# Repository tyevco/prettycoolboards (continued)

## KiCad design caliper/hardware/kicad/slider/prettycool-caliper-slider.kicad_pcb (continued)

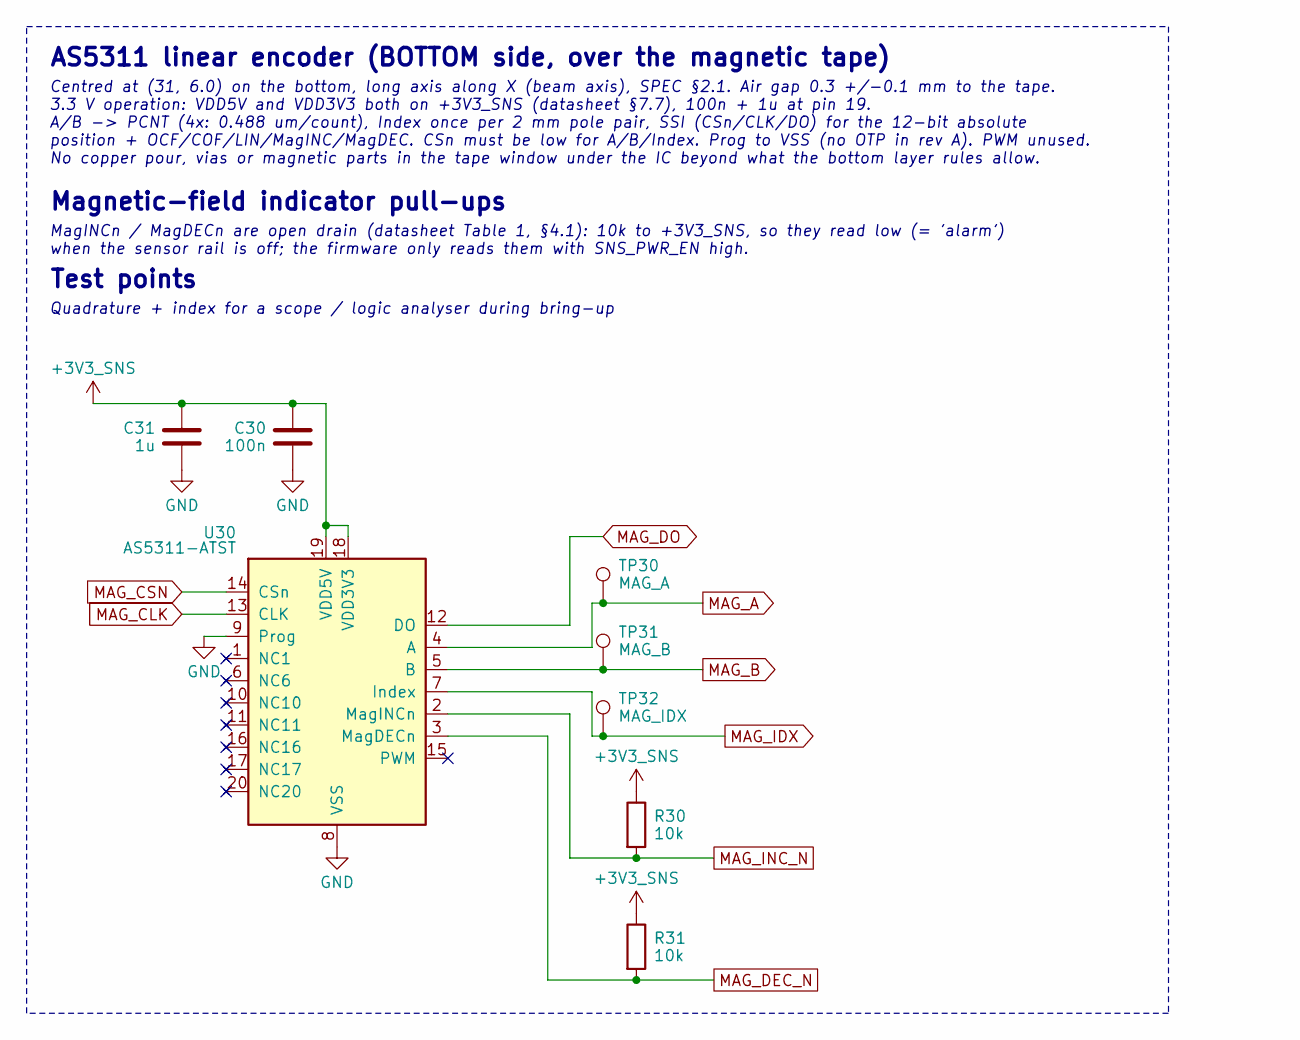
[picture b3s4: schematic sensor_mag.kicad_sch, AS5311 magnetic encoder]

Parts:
C30: 100n; C_0402_1005Metric; MPN CL05B104KO5NNNC; LCSC C1525
C31: 1u; C_0402_1005Metric; MPN CL05A105KA5NQNC; LCSC C52923
R30, R31: 10k; R_0402_1005Metric; MPN 0402WGF1002TCE; LCSC C25744
TP30: MAG_A; TestPoint_Pad_D1.0mm
TP31: MAG_B; TestPoint_Pad_D1.0mm
TP32: MAG_IDX; TestPoint_Pad_D1.0mm
U30: AS5311-ATST; TSSOP-20_4.4x6.5mm_P0.65mm; MPN AS5311-ATST; LCSC C22459687

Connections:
+3V3_SNS: C30.1, C31.1, R30.1, R31.1, U30.18 (VDD3V3), U30.19 (VDD5V); also elsewhere on the board
GND: C30.2, C31.2, U30.8 (VSS), U30.9 (Prog); also elsewhere on the board
MAG_A: TP30.1, U30.4 (A); also elsewhere on the board
MAG_B: TP31.1, U30.5 (B); also elsewhere on the board
MAG_CLK: U30.13 (CLK); also elsewhere on the board
MAG_CSN: U30.14 (CSn); also elsewhere on the board
MAG_DEC_N: R31.2, U30.3 (MagDECn); also elsewhere on the board
MAG_DO: U30.12 (DO); also elsewhere on the board
MAG_IDX: TP32.1, U30.7 (Index); also elsewhere on the board
MAG_INC_N: R30.2, U30.2 (MagINCn); also elsewhere on the board

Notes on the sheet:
AS5311 linear encoder (BOTTOM side, over the magnetic tape)
Centred at (31, 6.0) on the bottom, long axis along X (beam axis), SPEC §2.1. Air gap 0.3 +/-0.1 mm to the tape. 3.3 V operation: VDD5V and VDD3V3 both on +3V3_SNS (datasheet §7.7), 100n + 1u at pin 19. A/B -> PCNT (4x: 0.488 um/count), Index once per 2 mm pole pair, SSI (CSn/CLK/DO) for the 12-bit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
Magnetic-field indicator pull-ups
MagINCn / MagDECn are open drain (datasheet Table 1, §4.1): 10k to +3V3_SNS, so they read low (= 'alarm') when the sensor rail is off; the firmware only reads them with SNS_PWR_EN high.
Test points
Quadrature + index for a scope / logic analyser during bring-up

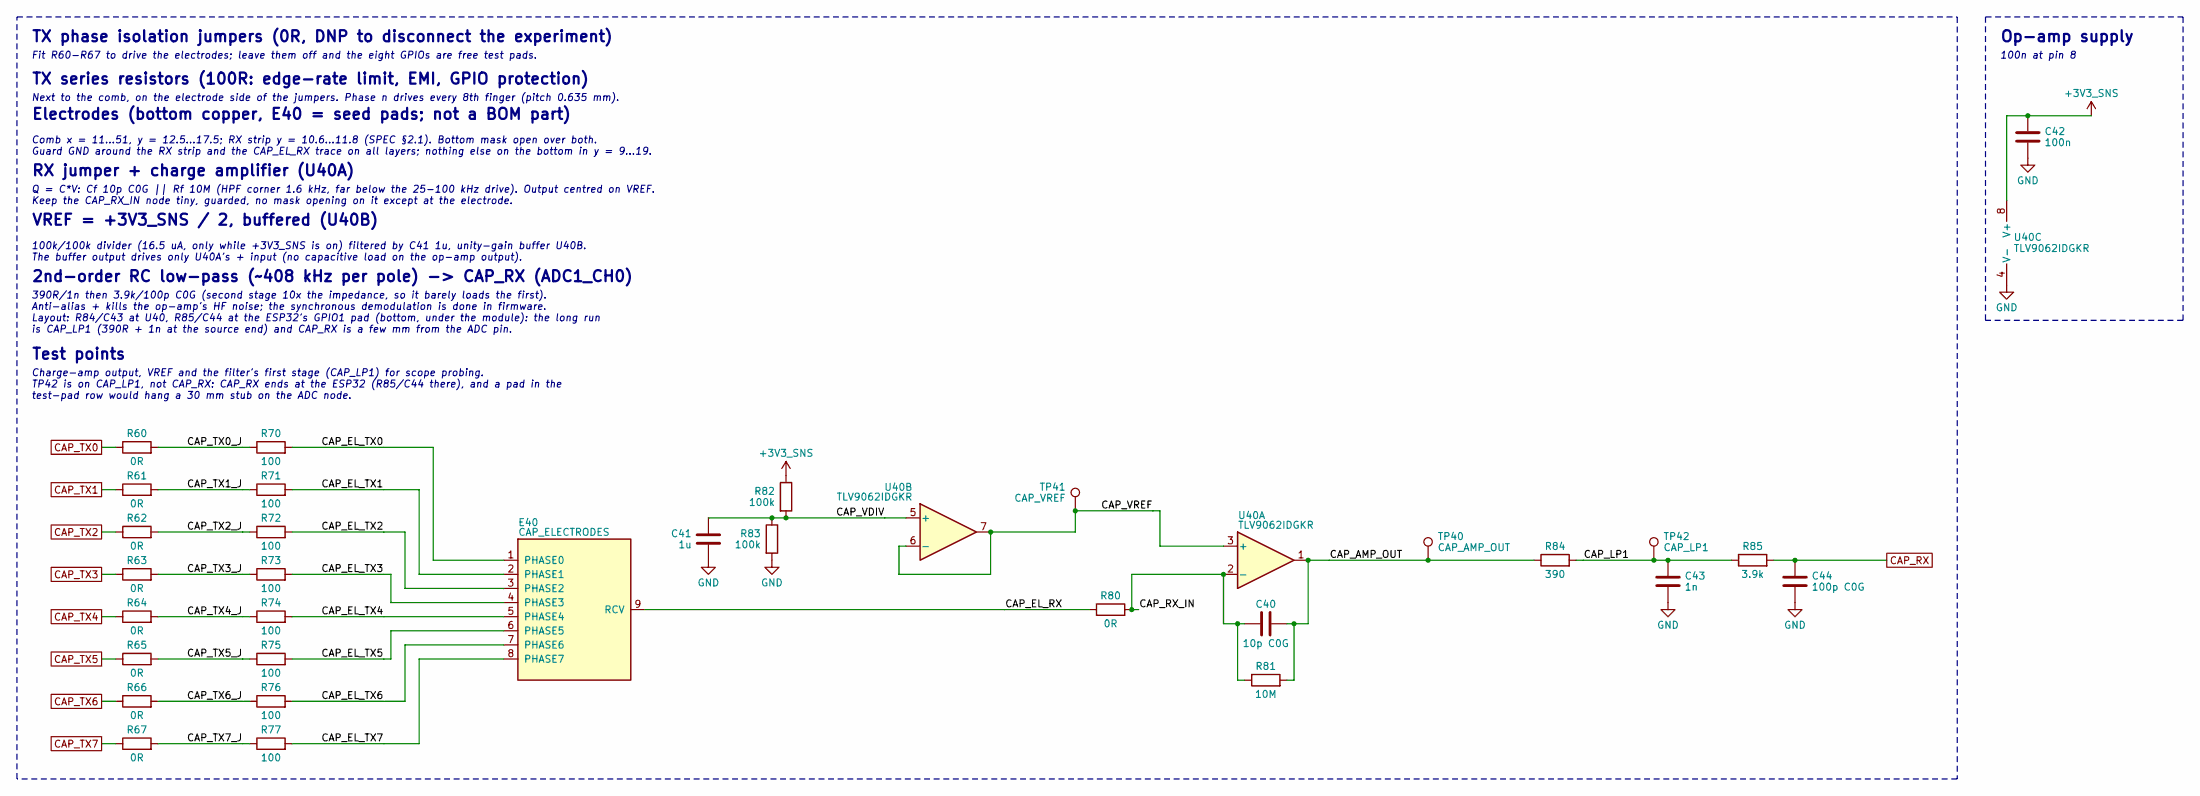
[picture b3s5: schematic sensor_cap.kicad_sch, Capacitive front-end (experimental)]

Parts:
C40: 10p C0G; C_0402_1005Metric; MPN 0402CG100J500NT; LCSC C1545
C41: 1u; C_0402_1005Metric; MPN CL05A105KA5NQNC; LCSC C52923
C42: 100n; C_0402_1005Metric; MPN CL05B104KO5NNNC; LCSC C1525
C43: 1n; C_0402_1005Metric; MPN 0402B102K500NT; LCSC C1523
C44: 100p C0G; C_0402_1005Metric; MPN 0402CG101J500NT; LCSC C1546
E40: CAP_ELECTRODES; Caliper_CapTX_Electrode_Seed_8Phase_P0.635mm
R60, R61, R62, R63, R64, R65, R66, R67, R80: 0R; R_0402_1005Metric; MPN 0402WGF0000TCE; LCSC C17168
R70, R71, R72, R73, R74, R75, R76, R77: 100; R_0402_1005Metric; MPN 0402WGF1000TCE; LCSC C25076
R81: 10M; R_0402_1005Metric; MPN 0402WGF1005TCE; LCSC C26082
R82, R83: 100k; R_0402_1005Metric; MPN 0402WGF1003TCE; LCSC C25741
R84: 390; R_0402_1005Metric; MPN 0402WGF3900TCE; LCSC C25109
R85: 3.9k; R_0402_1005Metric; MPN 0402WGF3901TCE; LCSC C51721
TP40: CAP_AMP_OUT; TestPoint_Pad_D1.0mm
TP41: CAP_VREF; TestPoint_Pad_D1.0mm
TP42: CAP_LP1; TestPoint_Pad_D1.0mm
U40: TLV9062IDGKR; VSSOP-8_3x3mm_P0.65mm; MPN TLV9062IDGKR; LCSC C398356

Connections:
+3V3_SNS: C42.1, R82.1, U40.8 (V+); also elsewhere on the board
/Capacitive front-end (experimental)/CAP_AMP_OUT: C40.2, R81.2, R84.1, TP40.1, U40.1
/Capacitive front-end (experimental)/CAP_EL_RX: E40.9 (RCV), R80.1
/Capacitive front-end (experimental)/CAP_EL_TX0: E40.1 (PHASE0), R70.2
/Capacitive front-end (experimental)/CAP_EL_TX1: E40.2 (PHASE1), R71.2
/Capacitive front-end (experimental)/CAP_EL_TX2: E40.3 (PHASE2), R72.2
/Capacitive front-end (experimental)/CAP_EL_TX3: E40.4 (PHASE3), R73.2
/Capacitive front-end (experimental)/CAP_EL_TX4: E40.5 (PHASE4), R74.2
/Capacitive front-end (experimental)/CAP_EL_TX5: E40.6 (PHASE5), R75.2
/Capacitive front-end (experimental)/CAP_EL_TX6: E40.7 (PHASE6), R76.2
/Capacitive front-end (experimental)/CAP_EL_TX7: E40.8 (PHASE7), R77.2
/Capacitive front-end (experimental)/CAP_LP1: C43.1, R84.2, R85.1, TP42.1
/Capacitive front-end (experimental)/CAP_RX_IN: C40.1, R80.2, R81.1, U40.2 (-)
/Capacitive front-end (experimental)/CAP_TX0_J: R60.2, R70.1
/Capacitive front-end (experimental)/CAP_TX1_J: R61.2, R71.1
/Capacitive front-end (experimental)/CAP_TX2_J: R62.2, R72.1
/Capacitive front-end (experimental)/CAP_TX3_J: R63.2, R73.1
/Capacitive front-end (experimental)/CAP_TX4_J: R64.2, R74.1
/Capacitive front-end (experimental)/CAP_TX5_J: R65.2, R75.1
/Capacitive front-end (experimental)/CAP_TX6_J: R66.2, R76.1
/Capacitive front-end (experimental)/CAP_TX7_J: R67.2, R77.1
/Capacitive front-end (experimental)/CAP_VDIV: C41.1, R82.2, R83.1, U40.5 (+)
/Capacitive front-end (experimental)/CAP_VREF: TP41.1, U40.3 (+), U40.6 (-), U40.7
CAP_RX: C44.1, R85.2; also elsewhere on the board
CAP_TX0: R60.1; also elsewhere on the board
CAP_TX1: R61.1; also elsewhere on the board
CAP_TX2: R62.1; also elsewhere on the board
CAP_TX3: R63.1; also elsewhere on the board
CAP_TX4: R64.1; also elsewhere on the board
CAP_TX5: R65.1; also elsewhere on the board
CAP_TX6: R66.1; also elsewhere on the board
CAP_TX7: R67.1; also elsewhere on the board
GND: C41.2, C42.2, C43.2, C44.2, R83.2, U40.4 (V-); also elsewhere on the board

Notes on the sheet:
TX phase isolation jumpers (0R, DNP to disconnect the experiment)
Fit R60-R67 to drive the electrodes; leave them off and the eight GPIOs are free test pads.
TX series resistors (100R: edge-rate limit, EMI, GPIO protection)
Next to the comb, on the electrode side of the jumpers. Phase n drives every 8th finger (pitch 0.635 mm).
Electrodes (bottom copper, E40 = seed pads; not a BOM part)
Comb x = 11...51, y = 12.5...17.5; RX strip y = 10.6...11.8 (SPEC §2.1). Bottom mask open over both. Guard GND around the RX strip and the CAP_EL_RX trace on all layers; nothing else on the bottom in y = 9...19.
RX jumper + charge amplifier (U40A)
Q = C*V: Cf 10p C0G || Rf 10M (HPF corner 1.6 kHz, far below the 25-100 kHz drive). Output centred on VREF. Keep the CAP_RX_IN node tiny, guarded, no mask opening on it except at the electrode.
VREF = +3V3_SNS / 2, buffered (U40B)
100k/100k divider (16.5 uA, only while +3V3_SNS is on) filtered by C41 1u, unity-gain buffer U40B. The buffer output drives only U40A's + input (no capacitive load on the op-amp output).
2nd-order RC low-pass (~408 kHz per pole) -> CAP_RX (ADC1_CH0)
390R/1n then 3.9k/100p C0G (second stage 10x the impedance, so it barely loads the first). Anti-alias + kills the op-amp's HF noise; the synchronous demodulation is done in firmware. Layout: R84/C43 at U40, R85/C44 at the ESP32's GPIO1 pad (bottom, under the module): the long run is CAP_LP1 (390R +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
Test points
Charge-amp output, VREF and the filter's first stage (CAP_LP1) for scope probing. TP42 is on CAP_LP1, not CAP_RX: CAP_RX ends at the ESP32 (R85/C44 there), and a pad in the test-pad row would hang a 30 mm stub on the ADC node.
Op-amp supply
100n at pin 8

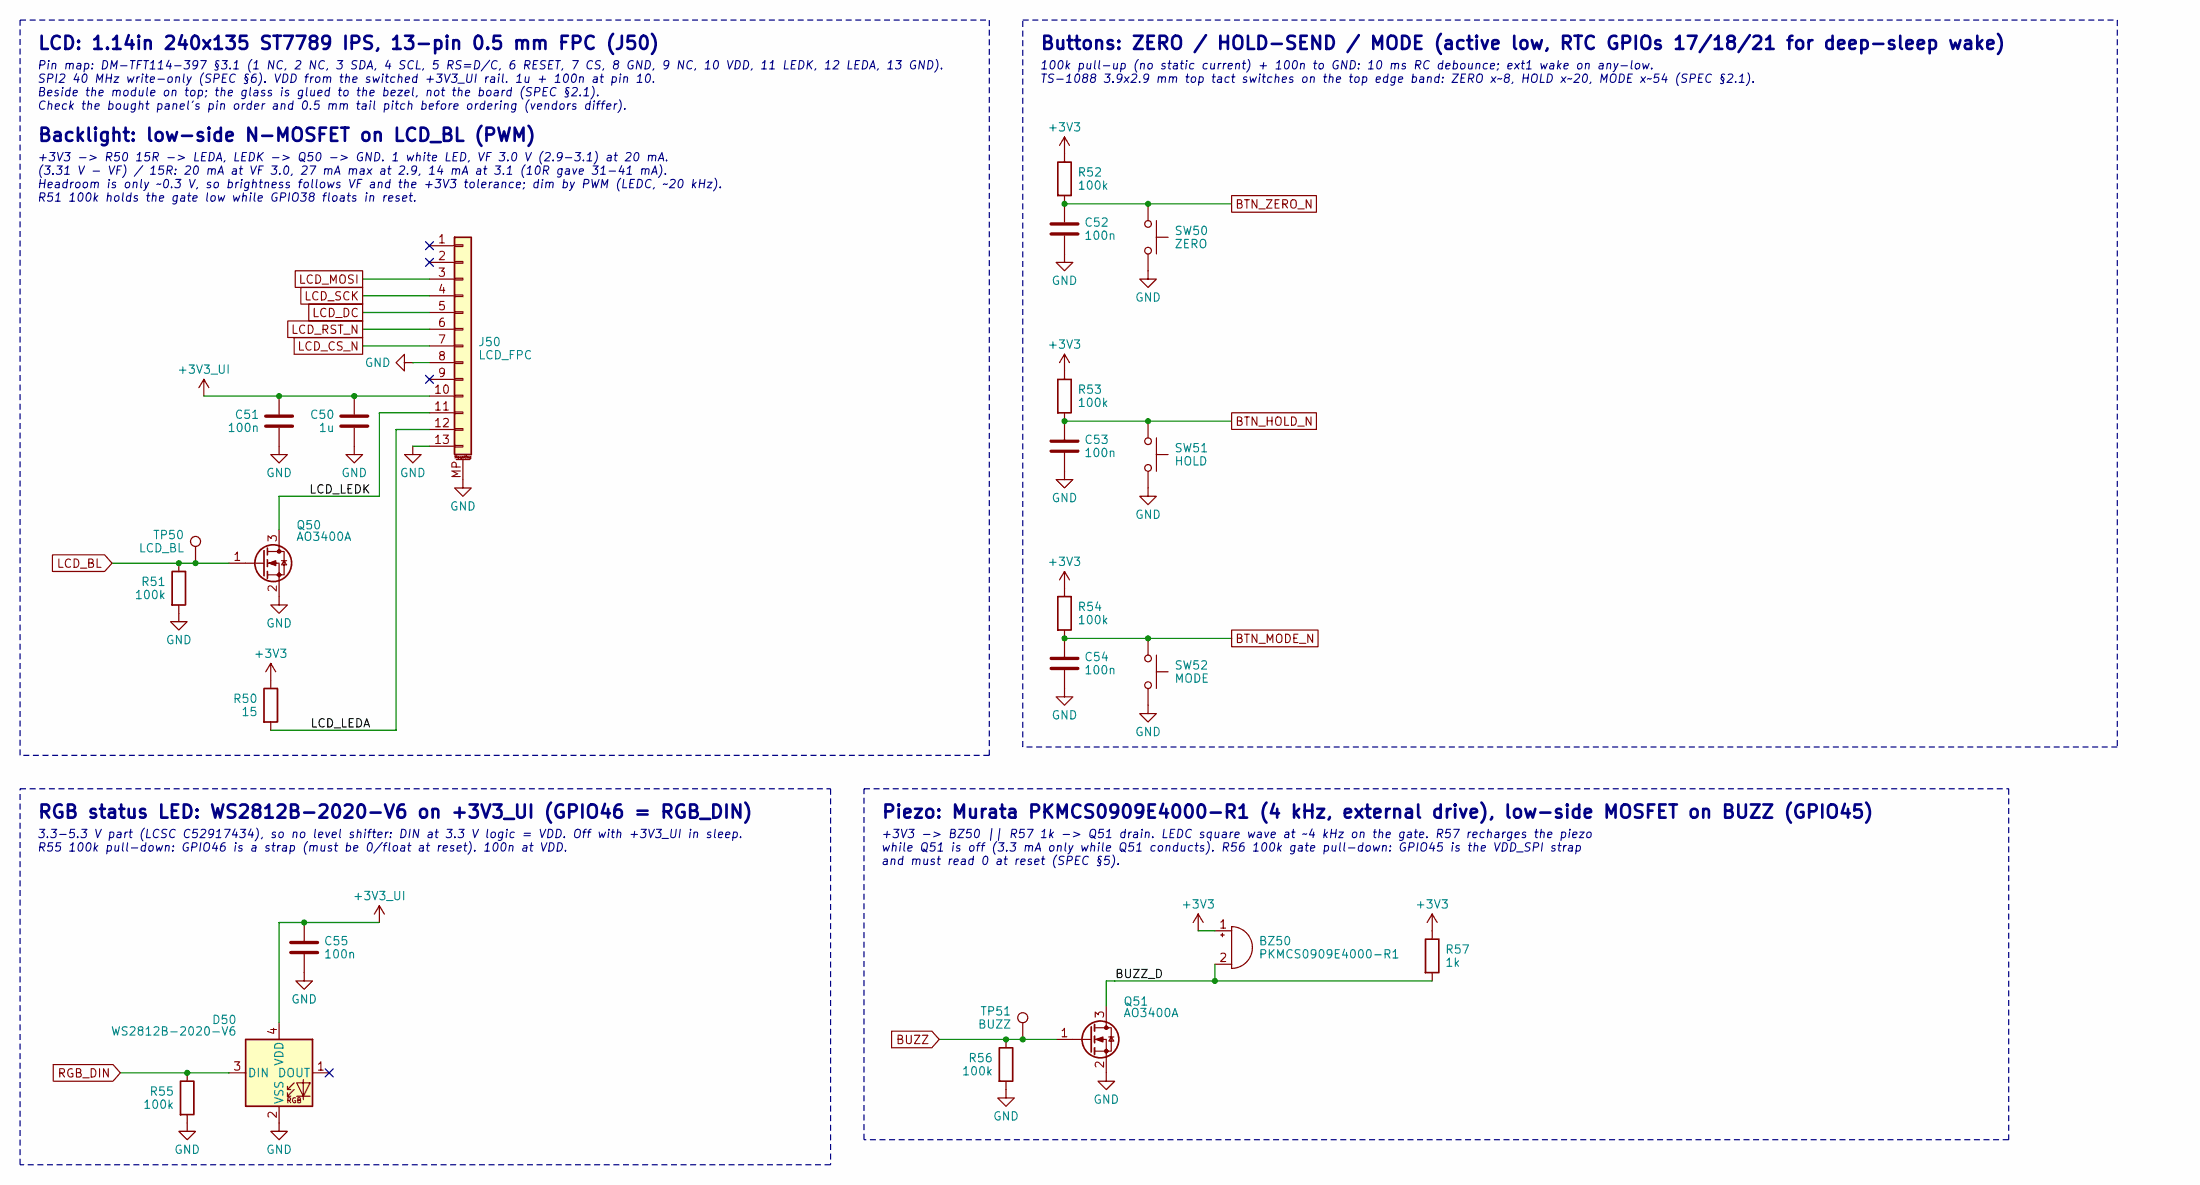
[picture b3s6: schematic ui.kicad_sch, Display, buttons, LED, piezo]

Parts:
BZ50: PKMCS0909E4000-R1; Buzzer_Murata_PKMCS0909E; MPN PKMCS0909E4000-R1; LCSC C910763
C50: 1u; C_0402_1005Metric; MPN CL05A105KA5NQNC; LCSC C52923
C51, C52, C53, C54, C55: 100n; C_0402_1005Metric; MPN CL05B104KO5NNNC; LCSC C1525
D50: WS2812B-2020-V6; LED_WS2812B-2020_PLCC4_2.0x2.0mm; MPN WS2812B-2020-V6; LCSC C52917434
J50: LCD_FPC; HDGC_0.5K-AX-13PWB_1x13-1MP_P0.50mm_Horizontal; MPN 0.5K-AX-13PWB; LCSC C2911931
Q50, Q51: AO3400A; SOT-23; MPN AO3400A; LCSC C20917
R50: 15; R_0603_1608Metric; MPN 0603WAF150JT5E; LCSC C22810
R51, R52, R53, R54, R55, R56: 100k; R_0402_1005Metric; MPN 0402WGF1003TCE; LCSC C25741
R57: 1k; R_0402_1005Metric; MPN 0402WGF1001TCE; LCSC C11702
SW50: ZERO; SW_SPST_TS-1088-xR020; MPN TS-1088-AR02016; LCSC C720477
SW51: HOLD; SW_SPST_TS-1088-xR020; MPN TS-1088-AR02016; LCSC C720477
SW52: MODE; SW_SPST_TS-1088-xR020; MPN TS-1088-AR02016; LCSC C720477
TP50: LCD_BL; TestPoint_Pad_D1.0mm
TP51: BUZZ; TestPoint_Pad_D1.0mm

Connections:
+3V3: BZ50.1 (+), R50.1, R52.1, R53.1, R54.1, R57.1; also elsewhere on the board
+3V3_UI: C50.1, C51.1, C55.1, D50.4 (VDD), J50.10; also elsewhere on the board
/Display, buttons, LED, piezo/BUZZ_D: BZ50.2 (-), Q51.3 (D), R57.2
/Display, buttons, LED, piezo/LCD_LEDA: J50.12, R50.2
/Display, buttons, LED, piezo/LCD_LEDK: J50.11, Q50.3 (D)
BTN_HOLD_N: C53.1, R53.2, SW51.1; also elsewhere on the board
BTN_MODE_N: C54.1, R54.2, SW52.1; also elsewhere on the board
BTN_ZERO_N: C52.1, R52.2, SW50.1; also elsewhere on the board
BUZZ: Q51.1 (G), R56.1, TP51.1; also elsewhere on the board
GND: C50.2, C51.2, C52.2, C53.2, C54.2, C55.2, D50.2 (VSS), J50.8, J50.13, J50.MP (MountPin), Q50.2 (S), Q51.2 (S), R51.2, R55.2, R56.2, SW50.2, SW51.2, SW52.2; also elsewhere on the board
LCD_BL: Q50.1 (G), R51.1, TP50.1; also elsewhere on the board
LCD_CS_N: J50.7; also elsewhere on the board
LCD_DC: J50.5; also elsewhere on the board
LCD_MOSI: J50.3; also elsewhere on the board
LCD_RST_N: J50.6; also elsewhere on the board
LCD_SCK: J50.4; also elsewhere on the board
RGB_DIN: D50.3 (DIN), R55.1; also elsewhere on the board

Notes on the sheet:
LCD: 1.14in 240x135 ST7789 IPS, 13-pin 0.5 mm FPC (J50)
Pin map: DM-TFT114-397 §3.1 (1 NC, 2 NC, 3 SDA, 4 SCL, 5 RS=D/C, 6 RESET, 7 CS, 8 GND, 9 NC, 10 VDD, 11 LEDK, 12 LEDA, 13 GND). SPI2 40 MHz write-only (SPEC §6). VDD from the switched +3V3_UI rail. 1u + 100n at pin 10. Beside the module on top; the glass is glued to the bezel, not the board (SPEC §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
Backlight: low-side N-MOSFET on LCD_BL (PWM)
+3V3 -> R50 15R -> LEDA, LEDK -> Q50 -> GND. 1 white LED, VF 3.0 V (2.9-3.1) at 20 mA. (3.31 V - VF) / 15R: 20 mA at VF 3.0, 27 mA max at 2.9, 14 mA at 3.1 (10R gave 31-41 mA). Headroom is only ~0.3 V, so brightness follows VF and the +3V3 tolerance; dim by PWM (LEDC, ~20 kHz). R51 100k holds the g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
Buttons: ZERO / HOLD-SEND / MODE (active low, RTC GPIOs 17/18/21 for deep-sleep wake)
100k pull-up (no static current) + 100n to GND: 10 ms RC debounce; ext1 wake on any-low. TS-1088 3.9x2.9 mm top tact switches on the top edge band: ZERO x~8, HOLD x~20, MODE x~54 (SPEC §2.1).
RGB status LED: WS2812B-2020-V6 on +3V3_UI (GPIO46 = RGB_DIN)
3.3-5.3 V part (LCSC C52917434), so no level shifter: DIN at 3.3 V logic = VDD. Off with +3V3_UI in sleep. R55 100k pull-down: GPIO46 is a strap (must be 0/float at reset). 100n at VDD.
Piezo: Murata PKMCS0909E4000-R1 (4 kHz, external drive), low-side MOSFET on BUZZ (GPIO45)
+3V3 -> BZ50 || R57 1k -> Q51 drain. LEDC square wave at ~4 kHz on the gate. R57 recharges the piezo while Q51 is off (3.3 mA only while Q51 conducts). R56 100k gate pull-down: GPIO45 is the VDD_SPI strap and must read 0 at reset (SPEC §5).

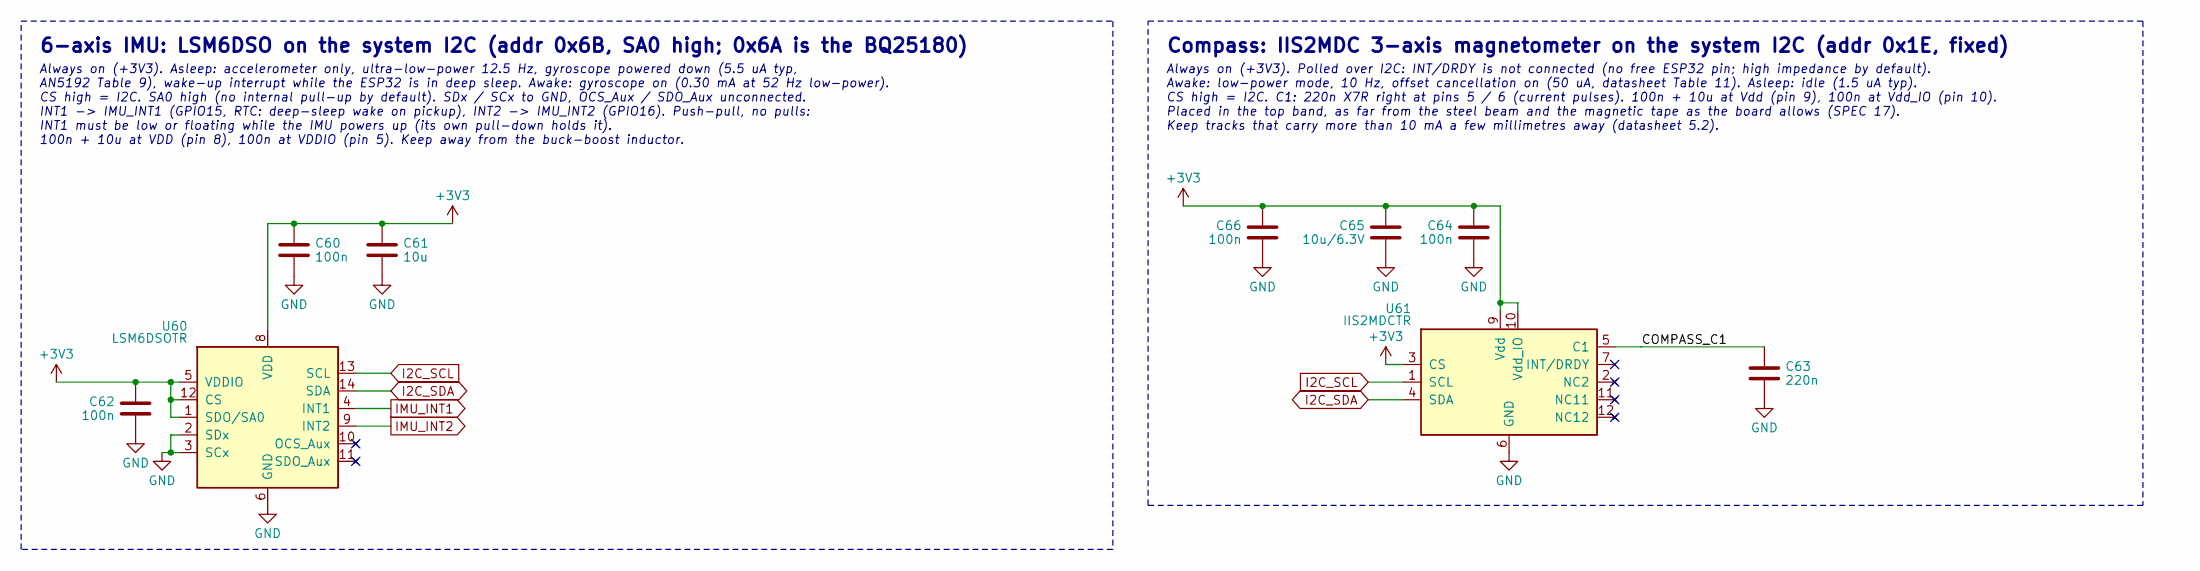
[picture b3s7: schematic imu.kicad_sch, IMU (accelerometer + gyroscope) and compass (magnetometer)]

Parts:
C60, C62, C64, C66: 100n; C_0402_1005Metric; MPN CL05B104KO5NNNC; LCSC C1525
C61: 10u; C_0603_1608Metric; MPN CL10A106KP8NNNC; LCSC C19702
C63: 220n; C_0402_1005Metric; MPN CL05B224KO5NNNC; LCSC C16772
C65: 10u/6.3V; C_0402_1005Metric; MPN CL05A106MQ5NUNC; LCSC C15525
U60: LSM6DSOTR; LGA-14_3x2.5mm_P0.5mm_LayoutBorder3x4y; MPN LSM6DSOTR; LCSC C2655100
U61: IIS2MDCTR; LGA-12_2x2mm_P0.5mm; MPN IIS2MDCTR; LCSC C2655002

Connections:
+3V3: C60.2, C61.2, C62.2, C64.2, C65.2, C66.2, U60.1 (SDO/SA0), U60.5 (VDDIO), U60.8 (VDD), U60.12 (CS), U61.3 (CS), U61.9 (Vdd), U61.10 (Vdd_IO); also elsewhere on the board
/IMU (accelerometer + gyroscope) and compass (magnetometer)/COMPASS_C1: C63.1, U61.5 (C1)
GND: C60.1, C61.1, C62.1, C63.2, C64.1, C65.1, C66.1, U60.2 (SDx), U60.3 (SCx), U60.6 (GND), U60.7 (GND), U61.6 (GND), U61.8 (GND); also elsewhere on the board
I2C_SCL: U60.13 (SCL), U61.1 (SCL); also elsewhere on the board
I2C_SDA: U60.14 (SDA), U61.4 (SDA); also elsewhere on the board
IMU_INT1: U60.4 (INT1); also elsewhere on the board
IMU_INT2: U60.9 (INT2); also elsewhere on the board

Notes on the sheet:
6-axis IMU: LSM6DSO on the system I2C (addr 0x6B, SA0 high; 0x6A is the BQ25180)
Always on (+3V3). Asleep: accelerometer only, ultra-low-power 12.5 Hz, gyroscope powered down (5.5 uA typ, AN5192 Table 9), wake-up interrupt while the ESP32 is in deep sleep. Awake: gyroscope on (0.30 mA at 52 Hz low-power). CS high = I2C. SA0 high (no internal pull-up by default). SDx / SCx to GN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
Compass: IIS2MDC 3-axis magnetometer on the system I2C (addr 0x1E, fixed)
Always on (+3V3). Polled over I2C: INT/DRDY is not connected (no free ESP32 pin; high impedance by default). Awake: low-power mode, 10 Hz, offset cancellation on (50 uA, datasheet Table 11). Asleep: idle (1.5 uA typ). CS high = I2C. C1: 220n X7R right at pins 5 / 6 (current pulses). 100n + 10u at V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

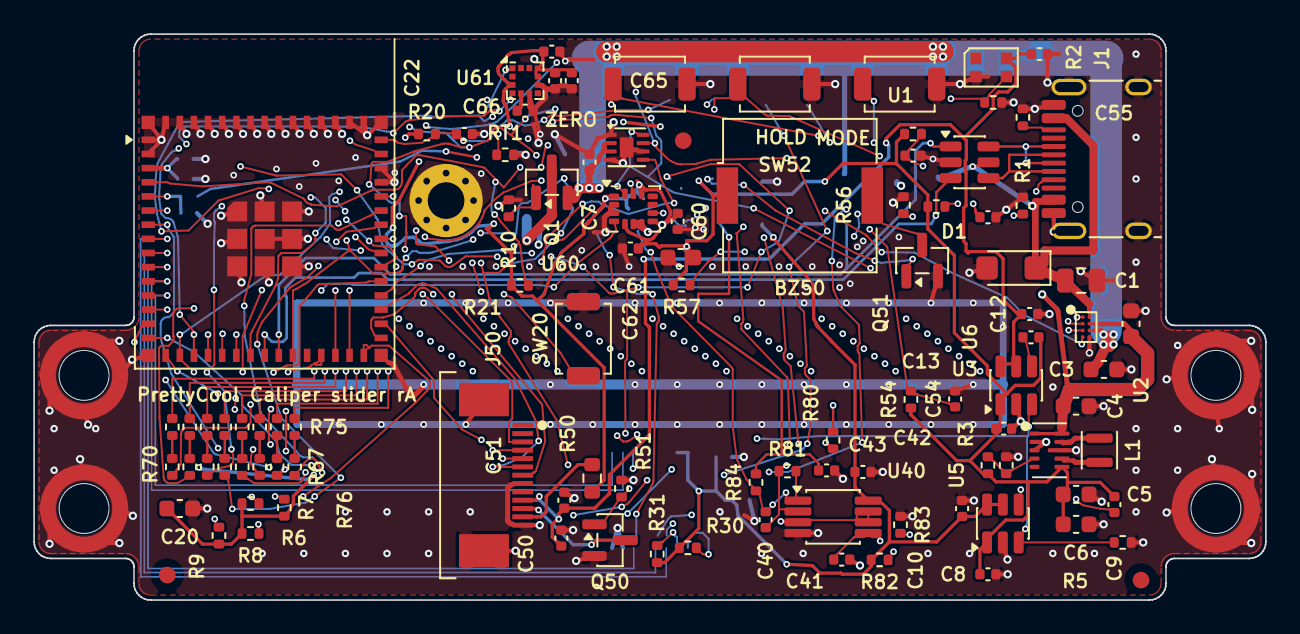
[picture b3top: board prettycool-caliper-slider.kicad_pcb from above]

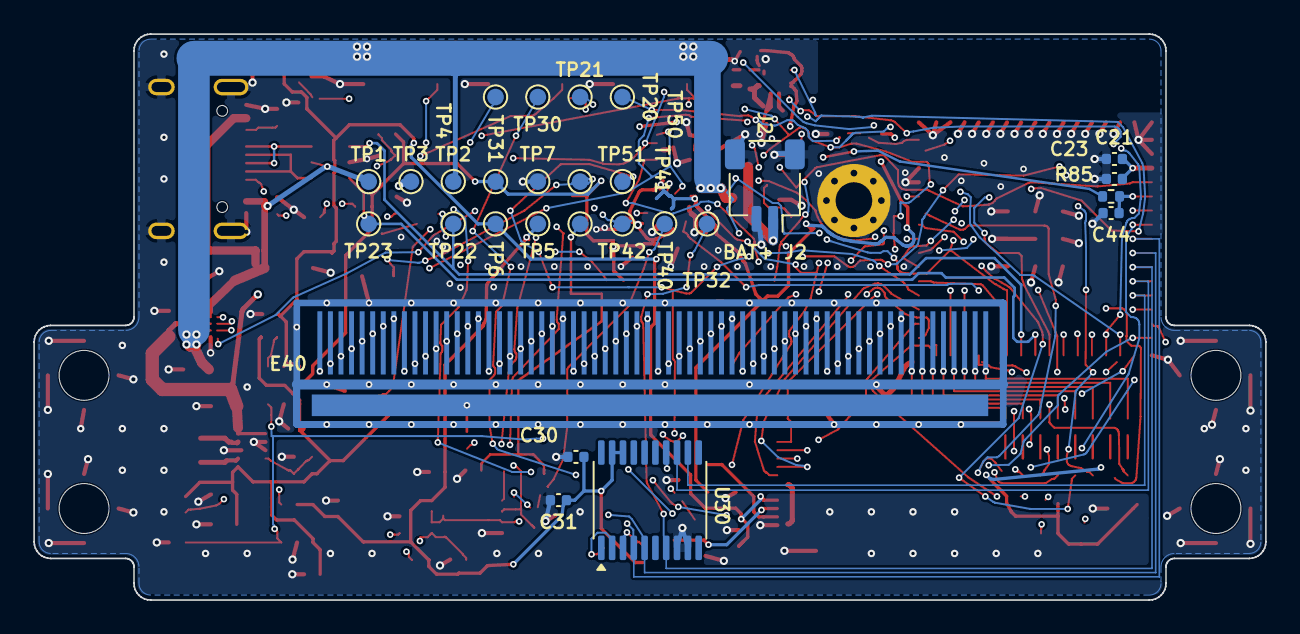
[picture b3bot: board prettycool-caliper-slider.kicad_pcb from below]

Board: 4 copper layers, 74.0 x 34.0 mm, 135 parts (28 on the bottom side), 82 nets.

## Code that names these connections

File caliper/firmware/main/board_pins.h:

/*
 * GENERATED by firmware/tools/gen_pins.py from caliper/hardware/design/nets.py. Do not edit.
 * nets.py REV A 2026-11-07
 */
#pragma once

#define BOARD_PINS_HASH "202d301f8ed3b0f1"
#define BOARD_REV "A"

/* GPIO number per net (ESP32-S3-MINI-1) */
#define PIN_BOOT_N      0  /* BOOT_N */
#define PIN_CAP_RX      1  /* CAP_RX */
#define PIN_FG_ALRT_N   2  /* FG_ALRT_N */
#define PIN_CHG_INT_N   3  /* CHG_INT_N */
#define PIN_MAG_A       4  /* MAG_A */
#define PIN_MAG_B       5  /* MAG_B */
#define PIN_MAG_IDX     6  /* MAG_IDX */
#define PIN_MAG_CLK     7  /* MAG_CLK */
#define PIN_MAG_DO      8  /* MAG_DO */
#define PIN_MAG_CSN     9  /* MAG_CSN */
#define PIN_MAG_INC_N  10  /* MAG_INC_N */
#define PIN_MAG_DEC_N  11  /* MAG_DEC_N */
#define PIN_SNS_PWR_EN 12  /* SNS_PWR_EN */
#define PIN_I2C_SDA    13  /* I2C_SDA */
#define PIN_I2C_SCL    14  /* I2C_SCL */
#define PIN_IMU_INT1   15  /* IMU_INT1 */
#define PIN_IMU_INT2   16  /* IMU_INT2 */
#define PIN_BTN_ZERO_N 17  /* BTN_ZERO_N */
#define PIN_BTN_HOLD_N 18  /* BTN_HOLD_N */
#define PIN_USB_DM     19  /* USB_DM */
#define PIN_USB_DP     20  /* USB_DP */
#define PIN_BTN_MODE_N 21  /* BTN_MODE_N */
#define PIN_LCD_SCK    33  /* LCD_SCK */
#define PIN_LCD_MOSI   34  /* LCD_MOSI */
#define PIN_LCD_CS_N   35  /* LCD_CS_N */
#define PIN_LCD_DC     36  /* LCD_DC */
#define PIN_LCD_RST_N  37  /* LCD_RST_N */
#define PIN_LCD_BL     38  /* LCD_BL */
#define PIN_CAP_TX0    39  /* CAP_TX0 */
#define PIN_CAP_TX1    40  /* CAP_TX1 */
#define PIN_CAP_TX2    41  /* CAP_TX2 */
#define PIN_CAP_TX3    42  /* CAP_TX3 */
#define PIN_CAP_TX6    43  /* CAP_TX6 */
#define PIN_CAP_TX7    44  /* CAP_TX7 */
#define PIN_BUZZ       45  /* BUZZ */
#define PIN_RGB_DIN    46  /* RGB_DIN */
#define PIN_CAP_TX4    47  /* CAP_TX4 */
#define PIN_CAP_TX5    48  /* CAP_TX5 */

/* 7-bit I2C addresses */
#define I2C_ADDR_BQ25180    0x6A
#define I2C_ADDR_IIS2MDC    0x1E
#define I2C_ADDR_LSM6DSO    0x6B
#define I2C_ADDR_MAX17048   0x36

/* CAP_TX0..7 in phase order, for the dedicated-GPIO bundle */
#define PIN_CAP_TX_LIST { PIN_CAP_TX0, PIN_CAP_TX1, PIN_CAP_TX2, PIN_CAP_TX3, PIN_CAP_TX4, PIN_CAP_TX5, PIN_CAP_TX6, PIN_CAP_TX7 }

/* every GPIO above, for checks (test/host/test_pin_plan.c: each one is in the pin plan) */
#define BOARD_PINS_COUNT 38
#define BOARD_PINS_ALL { \
    PIN_BOOT_N, PIN_CAP_RX, PIN_FG_ALRT_N, PIN_CHG_INT_N, PIN_MAG_A, PIN_MAG_B, \
    PIN_MAG_IDX, PIN_MAG_CLK, PIN_MAG_DO, PIN_MAG_CSN, PIN_MAG_INC_N, PIN_MAG_DEC_N, \
    PIN_SNS_PWR_EN, PIN_I2C_SDA, PIN_I2C_SCL, PIN_IMU_INT1, PIN_IMU_INT2, PIN_BTN_ZERO_N, \
    PIN_BTN_HOLD_N, PIN_USB_DM, PIN_USB_DP, PIN_BTN_MODE_N, PIN_LCD_SCK, PIN_LCD_MOSI, \
    PIN_LCD_CS_N, PIN_LCD_DC, PIN_LCD_RST_N, PIN_LCD_BL, PIN_CAP_TX0, PIN_CAP_TX1, \
    PIN_CAP_TX2, PIN_CAP_TX3, PIN_CAP_TX6, PIN_CAP_TX7, PIN_BUZZ, PIN_RGB_DIN, \
    PIN_CAP_TX4, PIN_CAP_TX5 \
}

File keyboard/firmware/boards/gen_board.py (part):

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    # motherboard signals
    tb = {
        "exp-int-gpios": gpio_ref(np["EXP_INT_N"], "GPIO_ACTIVE_LOW"),
        "slot-sync-gpios": gpio_ref(np["SLOT_SYNC"], "GPIO_ACTIVE_HIGH"),
        "rig-mark-gpios": gpio_ref(np["RIG_MARK"], "GPIO_ACTIVE_HIGH"),
        "rig-trig-gpios": gpio_ref(np["RIG_TRIG"], "GPIO_ACTIVE_HIGH"),
    }
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            else:
                gl.append(exp_ref(m, f"S{n}_{sig}", "GPIO_ACTIVE_HIGH"))
        w(f"\t\t\tg-gpios = {', '.join(gl)};")
        w(f"\t\t\tcs-gpios = {gpio_ref(sm['CS0_N'], 'GPIO_ACTIVE_LOW')}, {gpio_ref(sm['CS1_N'], 'GPIO_ACTIVE_LOW')};")
        w(f"\t\t\tirq-gpios = {gpio_ref(sm['IRQ_N'], 'GPIO_ACTIVE_LOW')};")
        if "BKIN" in m.mcu_func.get(sm["IRQ_N"], ("",))[0]:
            w("\t\t\t/* TIM1_BKIN: never gpio_pin_configure() it while TIM1 runs (SPEC §5.3). */")
            w("\t\t\tirq-is-tim1-bkin;")
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    w("/* USB high speed on the embedded PHY (SPEC §7.1, §8.2). USB_SOF (PA8) to J_RIG; the OTG core drives it only")
    w(" * once its SOF output is enabled, which Zephyr v4.5.0 does not do. */")
    w("zephyr_udc0: &usbotg_hs {")
    w(f"\tpinctrl-0 = <&{pinctrl(np['USB_DM'])} &{pinctrl(np['USB_DP'])} &{pinctrl(np['USB_SOF'])}>;")
    w('\tpinctrl-names = "default";')
    w('\tstatus = "okay";')
    w("};")
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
